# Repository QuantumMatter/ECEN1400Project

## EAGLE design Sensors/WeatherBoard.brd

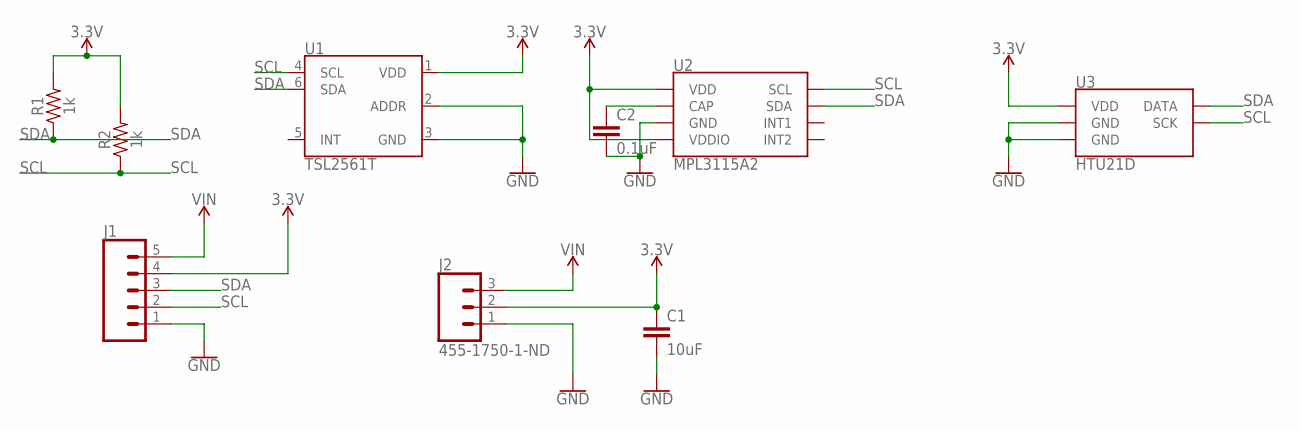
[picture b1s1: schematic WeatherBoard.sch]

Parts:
C1: 10uF; 1206
C2: 0.1uF; 0603
J1: CONN_05; 1X05
J2: 455-1750-1-ND; 1X03
R1, R2: 1k; 0603
U1: TSL2561T; TMB-6
U2: MPL3115A2; LGA-8-5X3
U3: HTU21D; DFN-6-3X3-HTU21D

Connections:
3.3V: C1.1, J1.4, J2.2, R1.2, R2.2, U1.1 (VDD), U2.1 (VDD), U2.4 (VDDIO), U3.VDD
GND: C1.2, C2.2, J1.1, J2.1, U1.2 (ADDR), U1.3 (GND), U2.3 (GND), U3.7 (GND), U3.GND
unnamed: C2.1, U2.2 (CAP)
SCL: J1.2, R2.1, U1.4 (SCL), U2.8 (SCL), U3.SCK
SDA: J1.3, R1.1, U1.6 (SDA), U2.7 (SDA), U3.DATA
VIN: J1.5, J2.3

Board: 2 copper layers, 9 parts (0 on the bottom side), 6 nets, no tracks yet.

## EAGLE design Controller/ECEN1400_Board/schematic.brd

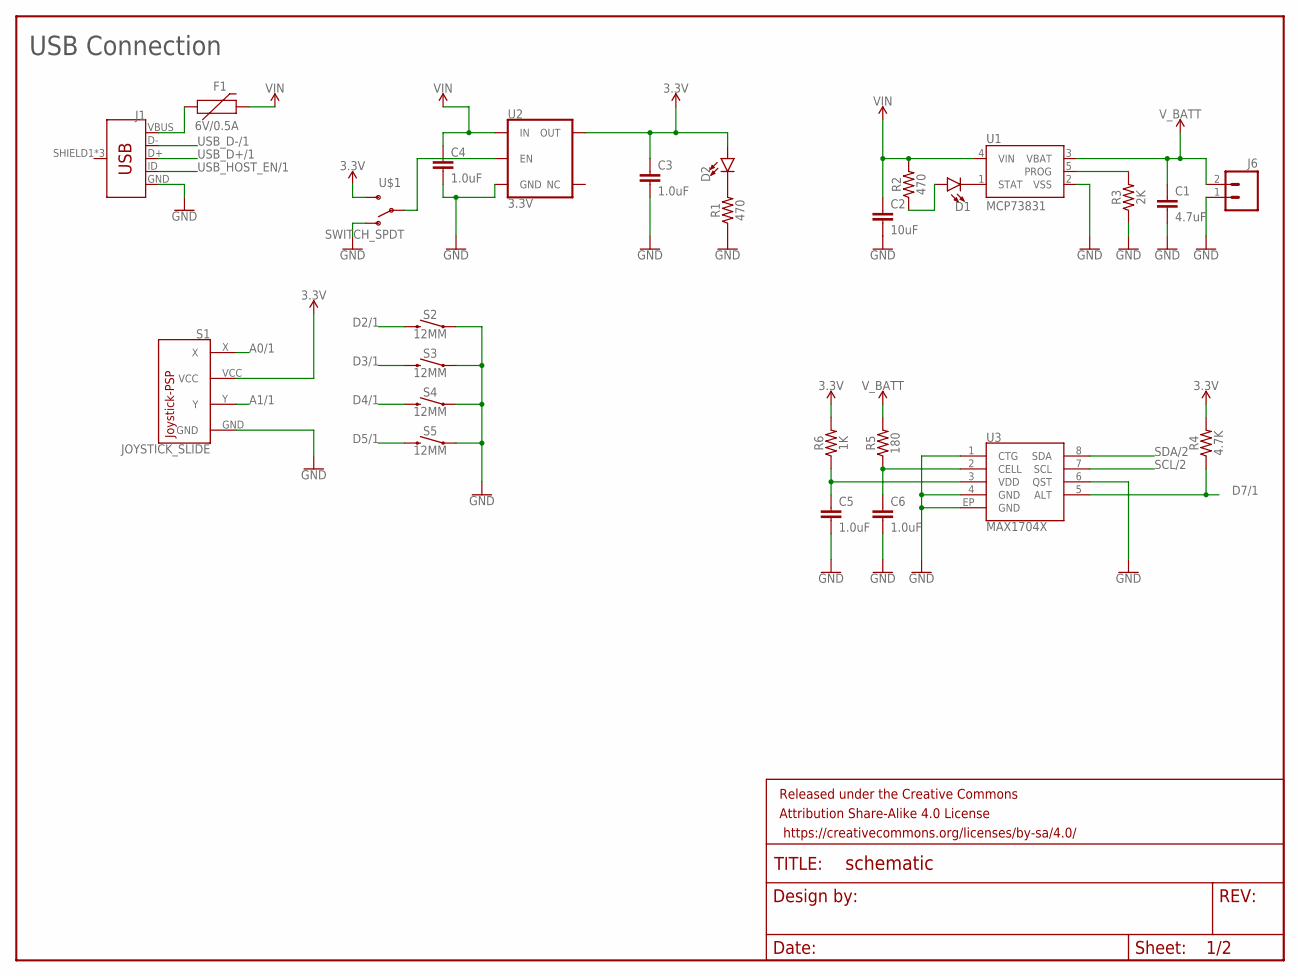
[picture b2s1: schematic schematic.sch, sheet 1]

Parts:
C1: 4.7uF; 1206
C2: 10uF; 1206
C3, C4, C5, C6: 1.0uF; 1206
D1, D2: LED-FKIT-1206; FKIT-LED-1206
F1: 6V/0.5A; 1206
FRAME1: FRAME-LETTERNO_PACKAGE; DUMMY
J1: USB_MICRO-B_FEMALE-SMT; USB-B-MICRO-SMD
J6: M021X02_NO_SILK; 1X02_NO_SILK
R1, R2: 470; 1210
R3: 2K; 1210
R4: 4.7K; 1210
R5: 180; 1210
R6: 1K; 1210
S1: JOYSTICK_SLIDE; JOYSTICK-PSP1000
S2, S3, S4, S5: 12MM; TACTILE_SWITCH_SMD_12MM
U1: MCP73831; SOT23-5
U2: 3.3V; SOT23-5
U3: MAX1704X; TDFN-8
U$1: SWITCH_SPDT; KPS-1290

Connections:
3.3V: C3.1, D2.A, R4.2, R6.2, S1.VCC, U2.5 (OUT), U$1.S; also elsewhere on the board
A0/1: S1.X; also elsewhere on the board
A1/1: S1.Y; also elsewhere on the board
D2/1: S2.3 (2); also elsewhere on the board
D3/1: S3.3 (2); also elsewhere on the board
D4/1: S4.3 (2); also elsewhere on the board
D5/1: S5.3 (2); also elsewhere on the board
D7/1: R4.1, U3.5 (ALT); also elsewhere on the board
GND: C1.2, C2.2, C3.2, C4.2, C5.2, C6.2, J1.GND, J6.1, R1.1, R3.1, S1.GND, S2.1, S3.1, S4.1, S5.1, U1.2 (VSS), U2.2 (GND), U3.1 (CTG), U3.4 (GND), U3.6 (QST), U3.EP (GND), U$1.O; also elsewhere on the board
unnamed: C5.1, R6.1, U3.3 (VDD)
unnamed: C6.1, R5.1, U3.2 (CELL)
unnamed: D1.A, R2.1
unnamed: D1.C, U1.1 (STAT)
unnamed: U2.3 (EN), U$1.P
unnamed: R3.2, U1.5 (PROG)
unnamed: F1.1, J1.VBUS
unnamed: D2.C, R1.2
SCL/2: U3.7 (SCL)
SDA/2: U3.8 (SDA)
USB_D+/1: J1.D+; also elsewhere on the board
USB_D-/1: J1.D-; also elsewhere on the board
USB_HOST_EN/1: J1.ID
VIN: C2.1, C4.1, F1.2, R2.2, U1.4 (VIN), U2.1 (IN)
V_BATT: C1.1, J6.2, R5.2, U1.3 (VBAT)

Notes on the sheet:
USB Connection

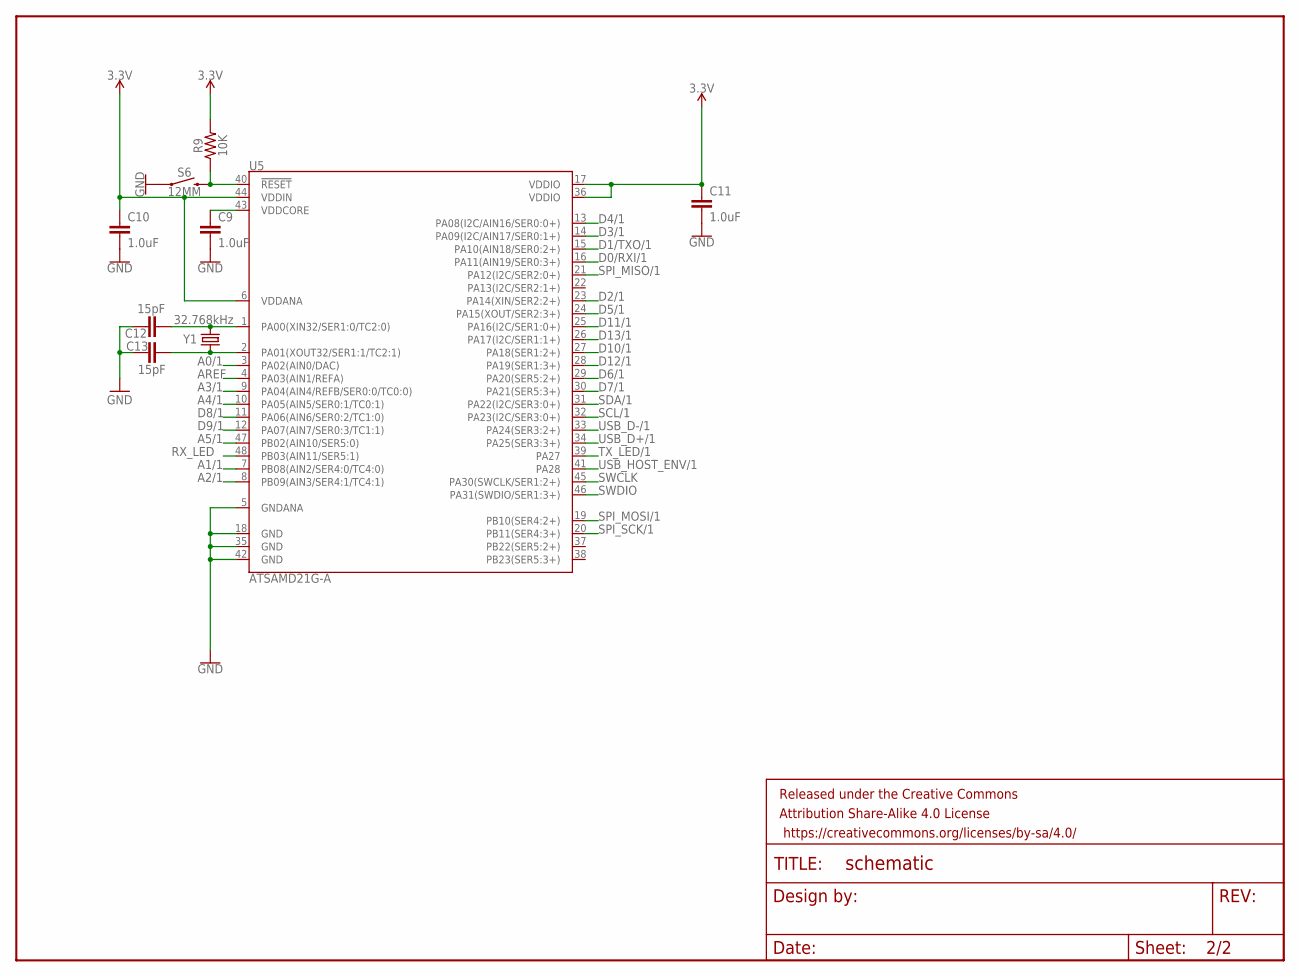
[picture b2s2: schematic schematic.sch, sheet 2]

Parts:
C9, C10, C11: 1.0uF; 1206
C12, C13: 15pF; 0603-CAP
FRAME2: FRAME-LETTERNO_PACKAGE; DUMMY
R9: 10K; 1210
S6: 12MM; TACTILE_SWITCH_SMD_12MM
U5: ATSAMD21G-A; TQFP-48
Y1: 32.768kHz; CRYSTAL-SMD-3.2X1.5MM

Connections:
3.3V: C10.1, C11.1, R9.2, U5.6 (VDDANA), U5.17 (VDDIO), U5.36 (VDDIO), U5.44 (VDDIN); also elsewhere on the board
A0/1: U5.3 (PA02(AIN0/DAC)); also elsewhere on the board
A1/1: U5.7 (PB08(AIN2/SER4:0/TC4:0)); also elsewhere on the board
A2/1: U5.8 (PB09(AIN3/SER4:1/TC4:1))
A3/1: U5.9 (PA04(AIN4/REFB/SER0:0/TC0:0))
A4/1: U5.10 (PA05(AIN5/SER0:1/TC0:1))
A5/1: U5.47 (PB02(AIN10/SER5:0))
AREF: U5.4 (PA03(AIN1/REFA))
D0/RXI/1: U5.16 (PA11(AIN19/SER0:3+))
D1/TXO/1: U5.15 (PA10(AIN18/SER0:2+))
D2/1: U5.23 (PA14(XIN/SER2:2+)); also elsewhere on the board
D3/1: U5.14 (PA09(I2C/AIN17/SER0:1+)); also elsewhere on the board
D4/1: U5.13 (PA08(I2C/AIN16/SER0:0+)); also elsewhere on the board
D5/1: U5.24 (PA15(XOUT/SER2:3+)); also elsewhere on the board
D6/1: U5.29 (PA20(SER5:2+))
D7/1: U5.30 (PA21(SER5:3+)); also elsewhere on the board
D8/1: U5.11 (PA06(AIN6/SER0:2/TC1:0))
D9/1: U5.12 (PA07(AIN7/SER0:3/TC1:1))
D10/1: U5.27 (PA18(SER1:2+))
D11/1: U5.25 (PA16(I2C/SER1:0+))
D12/1: U5.28 (PA19(SER1:3+))
D13/1: U5.26 (PA17(I2C/SER1:1+))
GND: C9.2, C10.2, C11.2, C12.1, C13.1, S6.1, U5.5 (GNDANA), U5.18 (GND), U5.35 (GND), U5.42 (GND); also elsewhere on the board
unnamed: C12.2, U5.1 (PA00(XIN32/SER1:0/TC2:0)), Y1.P$2 (2)
unnamed: C9.1, U5.43 (VDDCORE)
unnamed: C13.2, U5.2 (PA01(XOUT32/SER1:1/TC2:1)), Y1.P$1 (1)
RESET: R9.1, S6.3 (2), U5.40 (!RESET!)
RX_LED: U5.48 (PB03(AIN11/SER5:1))
SCL/1: U5.32 (PA23(I2C/SER3:0+))
SDA/1: U5.31 (PA22(I2C/SER3:0+))
SPI_MISO/1: U5.21 (PA12(I2C/SER2:0+))
SPI_MOSI/1: U5.19 (PB10(SER4:2+))
SPI_SCK/1: U5.20 (PB11(SER4:3+))
SWCLK: U5.45 (PA30(SWCLK/SER1:2+))
SWDIO: U5.46 (PA31(SWDIO/SER1:3+))
TX_LED/1: U5.39 (PA27)
USB_D+/1: U5.34 (PA25(SER3:3+)); also elsewhere on the board
USB_D-/1: U5.33 (PA24(SER3:2+)); also elsewhere on the board
USB_HOST_ENV/1: U5.41 (PA28)

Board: 2 copper layers, 37 parts (0 on the bottom side), 25 nets, no tracks yet.

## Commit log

2017-11-07 Added TCP socket files; started modifying server class to return client address and port with each read callback
2017-11-07 Added build file
2017-11-07 Added stream forwarding stuff
2017-11-08 started creating rpiclient program
2017-11-08 test
2017-11-08 Added email ip script
2017-11-08 Fixed email script
2017-11-08 Added LED Control through TCP Stream
2017-11-08 Added build script for RPi, fixed RPiMaster, updated ip email to read gmail password from a text file
2017-11-09 Added website project
2017-11-09 server changes
2017-11-09 Started creating database API
2017-11-09 Implemented push in API
2017-11-14 Started working on controller
2017-12-03 Added L293D class and beginning of custom weather board
2017-12-03 Fixed RPI Net classes
2017-12-03 Fixes
2017-12-03 Final
2017-12-03 delay
2017-12-03 remove delay
2017-12-04 Added ArduinoSlave stuff
2017-12-04 updated build script
2017-12-04 Added data scaler to ArduinoSlave
2017-12-04 added over warning
2017-12-04 Added color stuff
2017-12-04 fixed color stuff
2017-12-04 added color debugging
2017-12-04 sending only 255
2017-12-05 Added TrekManager to RPi
2017-12-05 Started creating Altimeter class
2017-12-05 New MPL test class
2017-12-05 Updated build script; started using python scripts for i2c devices
2017-12-05 Update MPL class
2017-12-05 MPL Fixes
2017-12-05 MPL testing
2017-12-05 MPL Update
2017-12-05 Uploading altimeter data to the server
2017-12-05 Added SI7021 class
2017-12-05 Double byte read fix
2017-12-05 SI7021 fixed
2017-12-05 Using Arduino to read the SI7021 data
2017-12-06 Added GPS scripts
2017-12-06 Updated python GPS script to write data to file
2017-12-06 fixed pi_gps
2017-12-06 Implemented Adafruit GPS in main
2017-12-09 Finished everything
2017-12-09 merge

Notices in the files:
parts and their libraries:
SparkFun-Capacitors: Licensing: Creative Commons ShareAlike 4.0 International - https://creativecommons.org/licenses/by-sa/4.0
SparkFun-Aesthetics: Released under the Creative Commons Attribution Share-Alike 4.0 License
SparkFun-Aesthetics: https://creativecommons.org/licenses/by-sa/4.0
